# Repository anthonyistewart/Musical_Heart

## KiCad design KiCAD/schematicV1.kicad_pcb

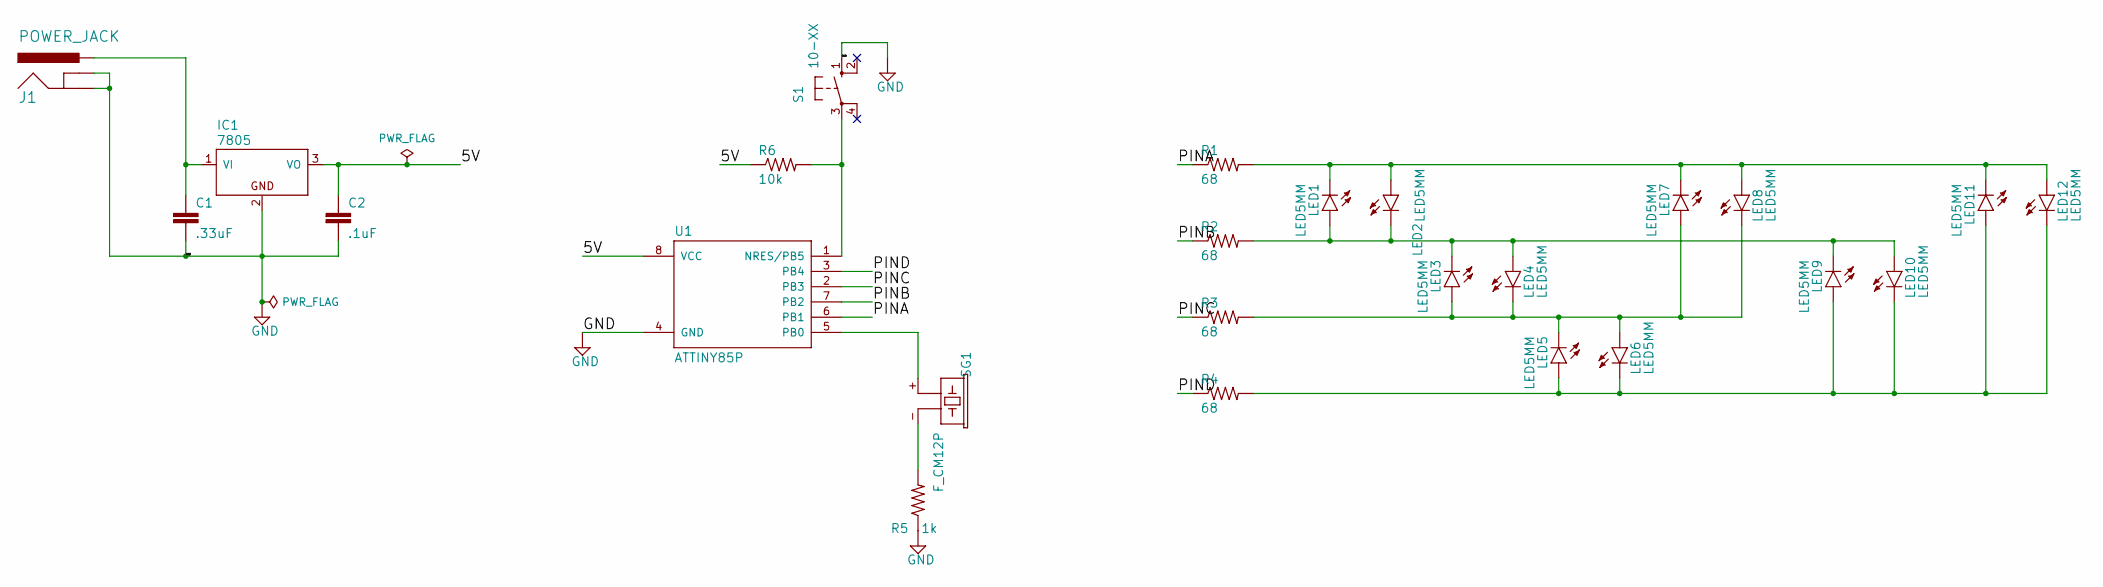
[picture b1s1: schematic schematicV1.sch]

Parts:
C1: .33uF; C2.5-3
C2: .1uF; C2.5-3
IC1: 7805; TO220H
J1: POWER_JACK; POWER_JACK_PTH
LED1, LED2, LED3, LED4, LED5, LED6, LED7, LED8, LED9, LED10, LED11, LED12: LED5MM
R1, R2, R3, R4: 68; 0204_5
R5: 1k; 0204_5
R6: 10k; 0204_5
S1: 10-XX; B3F-10XX
SG1: F_CM12P
U1: ATTINY85P; PDIP08_300MIL

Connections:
/5V: C2.1, IC1.3 (VO), R6.1, U1.8 (VCC)
/PINA: R1.1, U1.6 (PB1)
/PINB: R2.1, U1.7 (PB2)
/PINC: R3.1, U1.2 (PB3)
/PIND: R4.1, U1.3 (PB4)
GND: C1.2, C2.2, IC1.2 (GND), J1.GND, J1.GNDBREAK, R5.1, S1.1 (S), U1.4 (GND)
unnamed: C1.1, IC1.1 (VI), J1.PWR
unnamed: LED1.A, LED2.K (C), LED3.K (C), LED4.A, LED9.K (C), LED10.A, R2.2
unnamed: LED1.K (C), LED2.A, LED7.K (C), LED8.A, LED11.K (C), LED12.A, R1.2
unnamed: LED3.A, LED4.K (C), LED5.K (C), LED6.A, LED7.A, LED8.K (C), R3.2
unnamed: LED5.A, LED6.K (C), LED9.A, LED10.K (C), LED11.A, LED12.K (C), R4.2
unnamed: R5.2, SG1.- (2)
unnamed: R6.2, S1.3, U1.1 (NRES/PB5)
unnamed: SG1.+ (1), U1.5 (PB0)

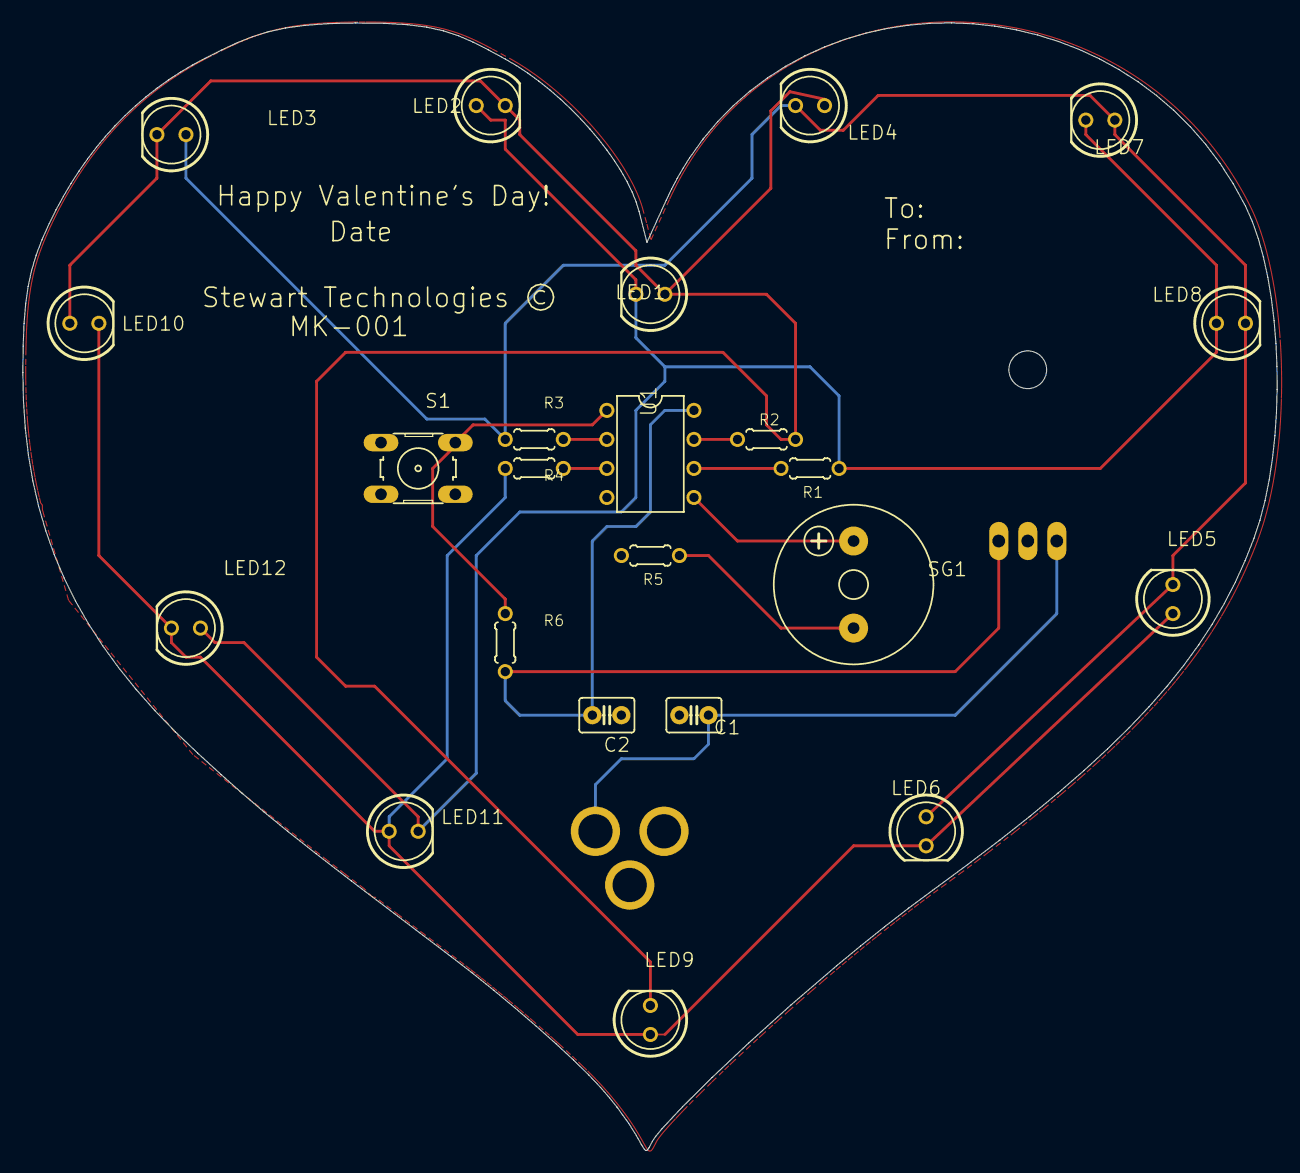
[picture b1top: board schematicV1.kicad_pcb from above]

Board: 2 copper layers, 109.8 x 98.7 mm, 25 parts (0 on the bottom side), 14 nets.
